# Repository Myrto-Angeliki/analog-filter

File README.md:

# Analog Front-End (AFE) Active Low-Pass Filter Module

A custom 2-layer printed circuit board (PCB) designed in KiCad for sensor signal conditioning in embedded hardware systems. This module combines a low-noise $3.3\text{V}$ Low-Dropout (LDO) power regulator with a 2nd-order active Sallen-Key low-pass filter ($f_c \approx 1.06\text{ kHz}$) and a unity-gain buffer stage to attenuate high-frequency noise prior to Analog-to-Digital Converter (ADC) sampling.

---

## Technical Specifications

* **Input Voltage ($V_{CC}$):** $5.0\text{V DC}$ nominal
* **Regulated Rail ($V_{DD}$):** $3.3\text{V DC}$ (AP2112K-3.3 LDO, up to $600\text{mA}$)
* **Filter Topology:** 2nd-Order Sallen-Key Low-Pass Filter + Output Voltage Follower Buffer
* **Characteristic Frequency ($f_c$):** $1.061\text{ kHz}$ ($-6\text{ dB}$)
* **Roll-off Rate:** $-40\text{ dB/decade}$
* **Active Components:** 
[MCP6002 Dual Rail-to-Rail CMOS Operational Amplifier (SOIC-8)](https://ww1.microchip.com/downloads/aemDocuments/documents/MSLD/ProductDocuments/DataSheets/MCP6001-1R-1U-2-4-1-MHz-Low-Power-Op-Amp-DS20001733L.pdf) , 
[AP2112K-3.3 LDO (SOT-23-5/SOT-25)](https://gr.mouser.com/datasheet/3/175/1/AP2112.pdf)
* **PCB Form Factor:** 2-Layer, $30\text{ mm} \times 40\text{ mm}$, hybrid SMT ICs with through-hole passives for rapid benchtop prototype assembly.

---

## Circuit Architecture & Calculations

### 1. Power Management & Decoupling
* **LDO Regulator:** AP2112K-3.3 steps down $5\text{V}$ $V_{CC}$ to a quiet $3.3\text{V}$ analog power rail.
* **Input/Output Capacitors:** $1\ \mu\text{F}$ MLCC on $V_{IN}$ and a $2.2\ \mu\text{F}$ MLCC on $V_{OUT}$. The $2.2\ \mu\text{F}$ value was selected over the $1\ \mu\text{F}$ minimum datasheet rating to account for ceramic DC-bias capacitance derating at $3.3\text{V}$ operating potential.
* **Local Decoupling:** A $100\text{ nF}$ ceramic capacitor is placed directly adjacent to the MCP6002 op-amp $V_{DD}$ pin (Pin 8) to mitigate high-frequency supply ripple.

### Sallen-Key Low-Pass Filter

The characteristic frequency ($f_0$) for the selected equal-component configuration ($R_1 = R_2 = 10\text{ k}\Omega$, $C_1 = C_2 = 15\text{ nF}$) is:

$$f_0 = \frac{1}{2\pi \sqrt{R_1 R_2 C_1 C_2}} \approx 1,061\text{ Hz}$$

Because $C_1 = C_2$, $R1 = R2$ and because tha operational amplifier is configured as a unity gain buffer (A = 1), the filter operates with $Q = 0.5$ (critically damped response):
* **Characteristic Frequency ($f_0$):** $1.061\text{ kHz}$ ($-6\text{ dB}$ attenuation)
* **Half-Power Cutoff Frequency ($f_{-3\text{dB}}$):** $\approx 683\text{ Hz}$ ($-3\text{ dB}$ attenuation)

### 3. Output Buffer
Op-Amp Channel B of MCP6002 is configured as a unity-gain voltage follower (connecting `OUTB` Pin 7 to `INB-` Pin 6). This presents a high input impedance to the filter stage and a low output drive impedance to downstream microcontrollers, eliminating loading effects on the filter's frequency response.

---

## LTspice Simulation

Prior to layout, the Sallen-Key low-pass filter was validated in LTspice using small-signal AC frequency analysis.

<br />

* **Simulation Directive:** `.ac dec 100 1 100k`
* **Passband Gain:** $0\text{ dB}$ up to $100\text{ Hz}$
* **$-6\text{ dB}$ frequency:** Verified at $\approx 1.06\text{ kHz}$
* **$-3\text{ dB}$ frequency:** Verified at $\approx 683\text{ Hz}$
* **Stopband Attenuation:** Confirmed $-40\text{ dB/decade}$ attenuation slope above cutoff frequency.

<table align="center">
    <thead>
        <tr>
            <th scope="col">Frequency at -3 dB</th>
            <th scope="col">Frequency at -6 dB</th>
            <th scope="col">Attenuation slope above cutoff frequency</th>
        </tr>
    </thead>
    <tbody> 
        <tr>
            <td>
                 
            </td>
            <td>
                
            </td>
            <td>
                
            </td>
        </tr> 
    </tbody> 
</table>
<p align="center">
  <em>Measurings on the Bode plot output for the V(out) trace (Gain = 1).</em>
</p>

<br />

---

## Board Pinout & Interface

| Header | Pin | Name | Type | Description |
| :--- | :--- | :--- | :--- | :--- |
| **Power (J1)** | 1 | `3.3V` | Power | $+3.3\text{V}$ Regulated Output Rail |
| | 2 | `VCC` | Power | $+5.0\text{V}$ Unregulated Power Input |
| | 3 | `GND` | Power | Common System Ground Plane |
| **Input (J2)** | 1 | `IN` | Analog Input | Raw Signal Input from Sensor |
| | 2 | `GND` | Power | Signal Ground |
| **Output (J3)**| 1 | `OUT` | Analog Output| Conditioned & Buffered Signal to ADC |
| | 2 | `GND` | Power | Signal Ground |

---

## PCB Layout Considerations

<table align="center">
    <thead>
        <tr>
            <th scope="col">PCB Front 3D View with Visible Components</th>
            <th scope="col">PCB Back 3D View with Visible Components</th>
        </tr>
    </thead>
    <tbody> 
        <tr>
            <!-- <th scope="row"></th> -->
            <td>
                <a href="docs\analog_filter_modules_front_models.png"> 
                     
                </a> 
            </td>
            <td>
                <a href="docs\analog_filter_modules_back_models.png"> 
                      
                </a> 
            </td>
        </tr> 
        <tr>
            <th scope="col">PCB Front 3D View</th>
            <th scope="col">PCB Back 3D View</th>
        </tr>
        <tr>
            <td>
                <a href="docs\analog_filter_modules_front.png"> 
                     
                </a> 
            </td>
            <td>
                <a href="docs\analog_filter_modules_back.png"> 
                      
                </a> 
            </td>
        </tr> 
    </tbody> 
</table>
<p align="center">
  <em>3D Views of the PCB design.</em>
</p>

<br />

* **Ground Pour Strategy:** Top (`F.Cu`) and Bottom (`B.Cu`) layers are poured with continuous `GND` copper fills to provide a low-impedance ground return path and improve thermal dissipation.
* **Component Placement:** Power routing and decoupling components are placed close to the board headers and active supply pins to minimize current loop inductance.
* **Signal Isolation:** Analog input and output traces are routed with high clearance from power lines to reduce crosstalk and noise coupling.

---

## Repository Structure

```text
.
├── docs/                 # LTspice schematics, Bode plot outputs, PCB Views, BOM
├── gbr/                  # Production Gerber and Excellon drill files for PCB manufacturing
├── kicad/
│   ├── Analog_Filter.kicad_sch  # KiCad schematic design
│   ├── Analog_Filter.kicad_pcb  # PCB layout & routing
│   └── Analog_Filter.pro        # KiCad project file
└── README.md             # Project overview

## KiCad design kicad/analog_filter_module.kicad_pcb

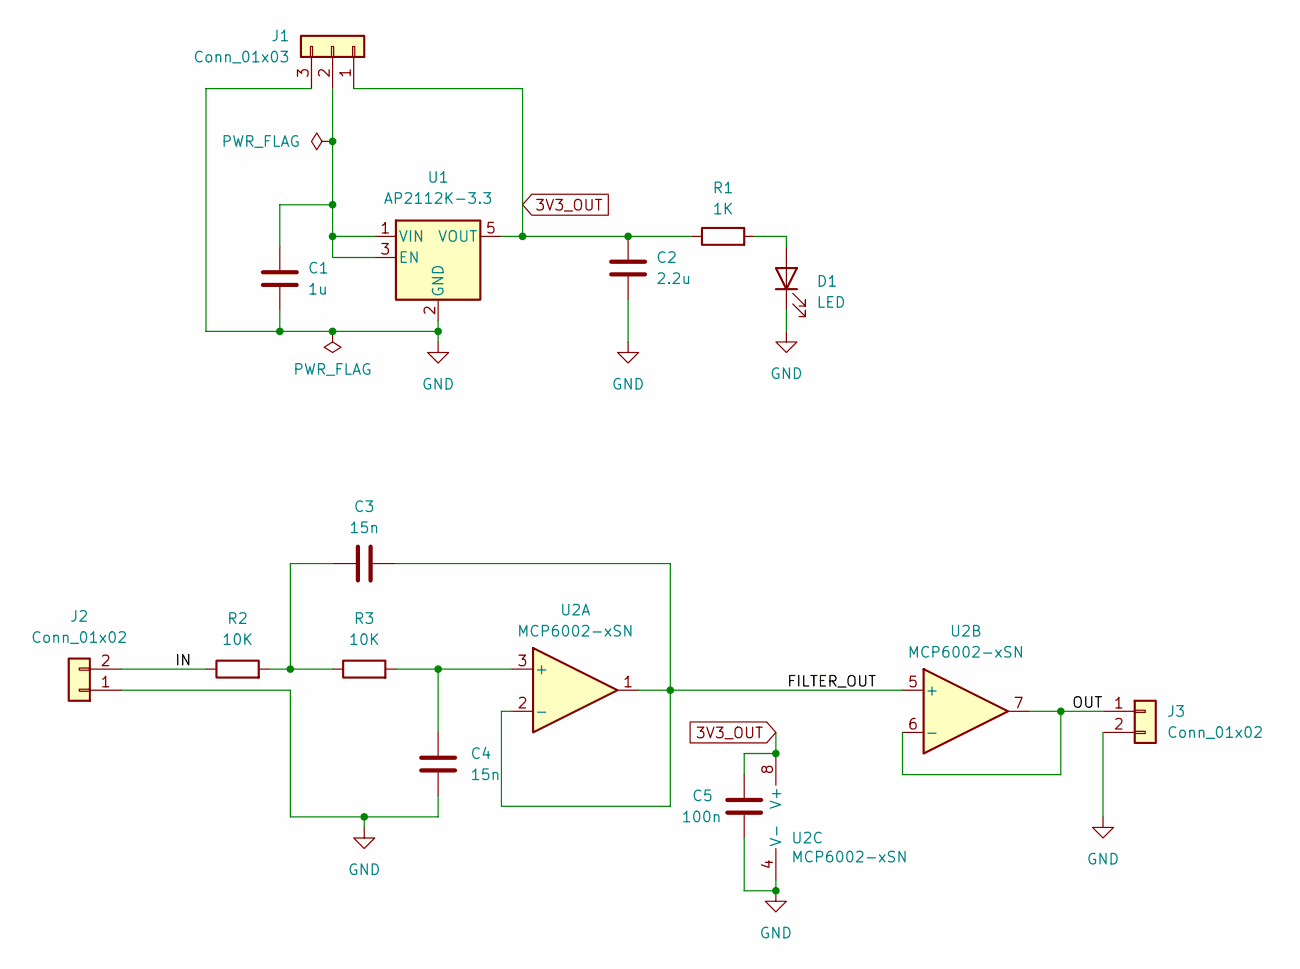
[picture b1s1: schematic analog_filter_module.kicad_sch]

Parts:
C1: 1u; C_Disc_D5.1mm_W3.2mm_P5.00mm
C2: 2.2u; C_Radial_D6.3mm_H7.0mm_P2.50mm
C3, C4: 15n; C_Disc_D6.0mm_W4.4mm_P5.00mm
C5: 100n; C_Disc_D5.1mm_W3.2mm_P5.00mm
D1: LED; LED_D5.0mm
J1: Conn_01x03; PinHeader_1x03_P2.54mm_Vertical
J2, J3: Conn_01x02; PinHeader_1x02_P2.54mm_Vertical
R1: 1K; R_Axial_DIN0207_L6.3mm_D2.5mm_P7.62mm_Horizontal
R2, R3: 10K; R_Axial_DIN0207_L6.3mm_D2.5mm_P7.62mm_Horizontal
U1: AP2112K-3.3; SOT-23-5
U2: MCP6002-xSN; SOIC-8_3.9x4.9mm_P1.27mm

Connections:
3V3_OUT: C2.1, C5.1, J1.1, R1.1, U1.5 (VOUT), U2.8 (V+)
/FILTER_OUT: C3.2, U2.1, U2.2 (-), U2.5 (+)
/IN: J2.2, R2.1
/OUT: J3.1, U2.6 (-), U2.7
GND: C1.2, C2.2, C4.2, C5.2, D1.1 (K), J1.3, J2.1, J3.2, U1.2 (GND), U2.4 (V-)
unnamed: C3.1, R2.2, R3.1
unnamed: D1.2 (A), R1.2
unnamed: C1.1, J1.2, U1.1 (VIN), U1.3 (EN)
unnamed: C4.1, R3.2, U2.3 (+)

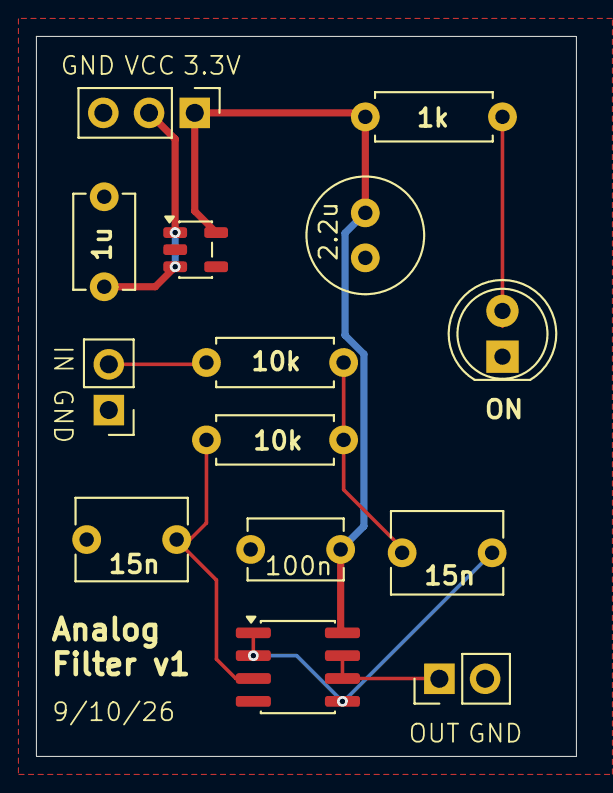
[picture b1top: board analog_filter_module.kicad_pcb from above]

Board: 4 copper layers, 30.0 x 40.0 mm, 14 parts (0 on the bottom side), 9 nets.
